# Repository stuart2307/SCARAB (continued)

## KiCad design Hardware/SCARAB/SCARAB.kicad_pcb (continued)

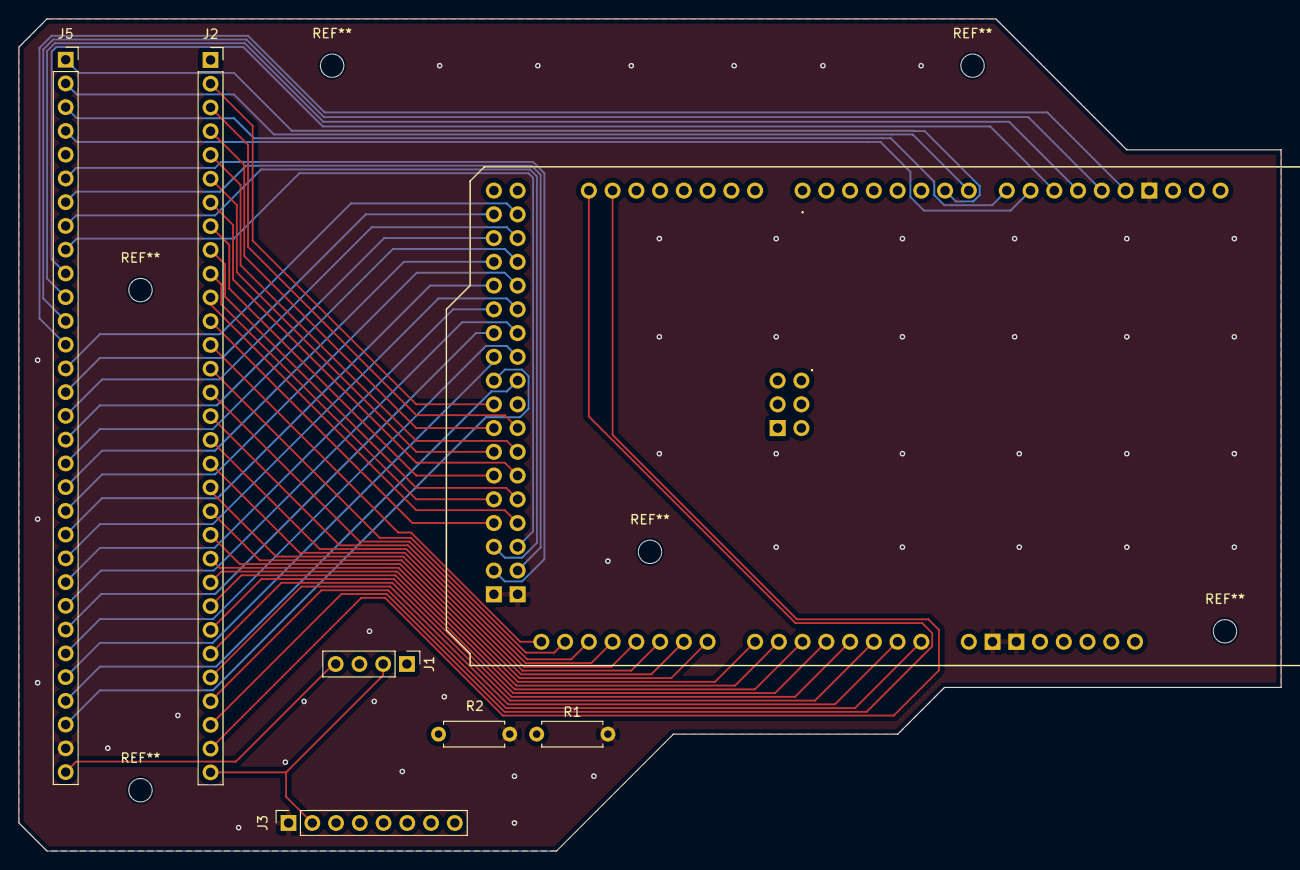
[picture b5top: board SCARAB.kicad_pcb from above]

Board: 2 copper layers, 135.0 x 89.0 mm, 7 parts (1 on the bottom side), 62 nets.

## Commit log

2025-10-05 Uploaded current Functional Specification
2025-10-06 Create GPL LICENSE
2025-10-06 Refactoring
2025-10-06 Changed name to SCARAB
2025-10-07 Worked on Functional Specification
2025-10-08 First Draft of Functional Specification
2025-10-08 Formatting
2025-10-09 Added to Research Doc
2025-10-11 Made progress on Research Document, finished 3.4
2025-10-12 More or less finished Research Document
2025-10-13 Ordered references correctly in Research Document
2025-10-15 Added Presentation
2025-10-19 Added some changes
2025-10-20 Updated research doc
2025-10-21 Added images to presentation
2025-11-09 Added research on microcontrollers.
2025-11-09 Added Project Plan to Functional Specification
2025-11-09 Added test header reader for SNES cartridges.
2025-11-09 Functional Spec Modified
2025-11-09 Elaborated on Microcontroller languages.
2025-11-30 Made progress on SNES Read and Test, provided CLI for SCARAB, added Circuit Diagrams.
2025-12-01 Added Design Document
2026-01-09 Added Schematics and PCB Design for SCARAB and accompanying SNES Module
2026-01-11 Added SCARAB Connector Footprint
2026-01-25 Updated SCARAB Presentation
2026-02-11 Added Mockups and added to Design Document
2026-02-12 Added more to Design Doc, including Mockups.
2026-02-13 Progressed in the SCARAB Device Development
2026-02-13 Made progress on Save Dumping
2026-02-13 Updated Design Document
2026-02-22 Finished Save Dumping and Restoring Functionality for SNES
2026-02-23 Added QtCreator GUI Progress
2026-03-09 Finished UI Designs
2026-03-11 UI Converted to py files, wrapper files started
2026-03-11 Progressed with UI
2026-03-12 UI Progress Made
2026-03-12 Added SCARAB Identification to the GUI program.
2026-03-12 Added SCARAB ID to the GUI program
2026-03-12 Added more screens to GUI
2026-03-12 Added all screens to GUI
2026-03-15 Added basic abstract Modules class
2026-03-16 Made progress on splitting code into a modular design
2026-03-17 Added some Save Browsing functionalities to GUI
2026-03-18 Added save dumping and restoring to GUI
2026-03-18 SCARAB Game details now show up in GUI
2026-03-19 Fixed bug leading to some save files not being dumped.
2026-04-07 Setup Check Health menu, and remade the SNES Module PCB.
2026-04-13 Created PCBs for more Cartridges, and fleshed out imagery in the PC Program
2026-04-15 Made Progress on game image display, and finished health checking + error handlng, along with an options menu
2026-04-16 Added image support and fixed bugs.
2026-04-19 Updated Final Report, Added NES Arduino Code
2026-04-19 Progress on Final Report + merging the INO files into one sketch
2026-04-20 Added website and progressed with final report.
2026-04-21 Fleshed out NES support, and added module image. Progressed with final report.
2026-04-22 Progressed with final report
2026-04-22 Finished NES, works for checksum.
2026-04-23 Created installer for SCARAB. Added user manual.
2026-04-24 bug fixes
2026-04-24 edited nes module board
2026-04-24 Commented Code, Converted documents to PDF.
2026-04-24 Finished SCARAB.
